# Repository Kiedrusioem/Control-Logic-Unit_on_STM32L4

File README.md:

# Control Logic Unit 

## Project Description
This project focuses on the design and development of a modular Control Logic Unit for a smart buildings system.

The project consists of the three modules:
- **Firware**
- **Extension Board**
- **Software**

## Features
###

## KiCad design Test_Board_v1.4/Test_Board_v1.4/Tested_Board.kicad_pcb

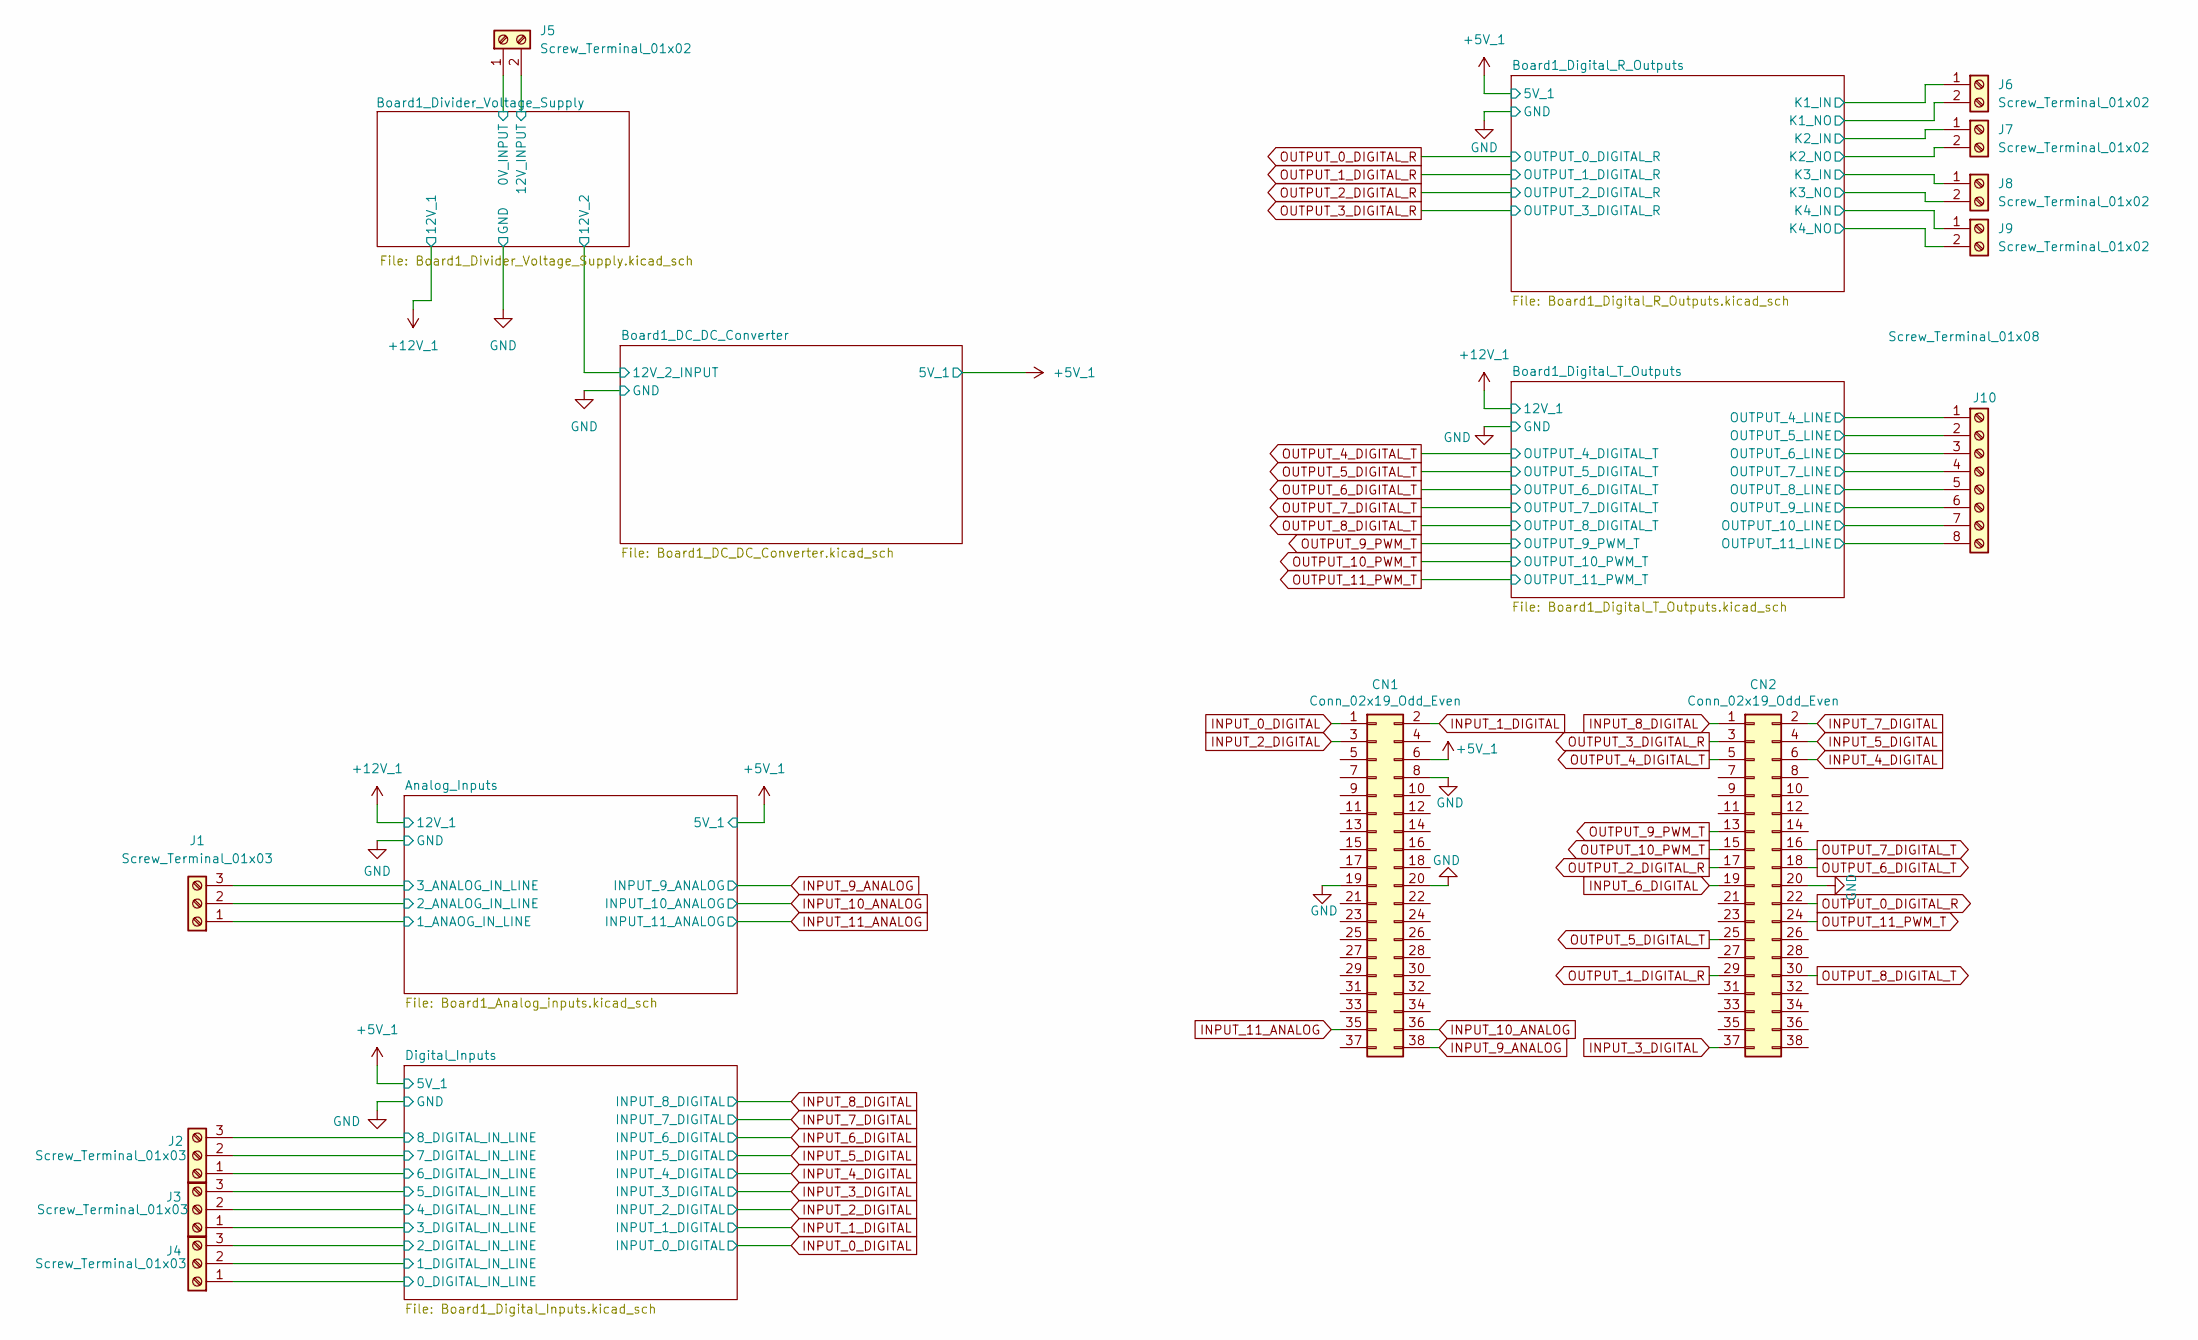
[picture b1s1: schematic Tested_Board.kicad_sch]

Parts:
CN1, CN2: Conn_02x19_Odd_Even; PinSocket_2x19_P2.54mm_Vertical
J1, J2, J3, J4: Screw_Terminal_01x03; TE_282837-3
J5, J6, J7, J8, J9: Screw_Terminal_01x02; TE_282836-2
J10: Screw_Terminal_01x08; TE_282834-8

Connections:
+5V_1: CN1.6; also elsewhere on the board
+12V_1: J5.2; also elsewhere on the board
/Analog_Inputs/1_ANAOG_IN_LINE: J1.1; also elsewhere on the board
/Analog_Inputs/2_ANALOG_IN_LINE: J1.2; also elsewhere on the board
/Analog_Inputs/3_ANALOG_IN_LINE: J1.3; also elsewhere on the board
/Board1_Digital_R_Outputs/K1_IN: J6.1; also elsewhere on the board
/Board1_Digital_R_Outputs/K1_NO: J6.2; also elsewhere on the board
/Board1_Digital_R_Outputs/K2_IN: J7.1; also elsewhere on the board
/Board1_Digital_R_Outputs/K2_NO: J7.2; also elsewhere on the board
/Board1_Digital_R_Outputs/K3_IN: J8.1; also elsewhere on the board
/Board1_Digital_R_Outputs/K3_NO: J8.2; also elsewhere on the board
/Board1_Digital_R_Outputs/K4_IN: J9.1; also elsewhere on the board
/Board1_Digital_R_Outputs/K4_NO: J9.2; also elsewhere on the board
/Board1_Digital_T_Outputs/OUTPUT_4_LINE: J10.1; also elsewhere on the board
/Board1_Digital_T_Outputs/OUTPUT_5_LINE: J10.2; also elsewhere on the board
/Board1_Digital_T_Outputs/OUTPUT_6_LINE: J10.3; also elsewhere on the board
/Board1_Digital_T_Outputs/OUTPUT_7_LINE: J10.4; also elsewhere on the board
/Board1_Digital_T_Outputs/OUTPUT_8_LINE: J10.5; also elsewhere on the board
/Board1_Digital_T_Outputs/OUTPUT_9_LINE: J10.6; also elsewhere on the board
/Board1_Digital_T_Outputs/OUTPUT_10_LINE: J10.7; also elsewhere on the board
/Board1_Digital_T_Outputs/OUTPUT_11_LINE: J10.8; also elsewhere on the board
/Digital_Inputs/MC33204_4_OPAMP_2_P_IN: J4.1; also elsewhere on the board
/Digital_Inputs/MC33204_4_OPAMP_3_P_IN: J4.2; also elsewhere on the board
/Digital_Inputs/MC33204_4_OPAMP_4_P_IN: J4.3; also elsewhere on the board
/Digital_Inputs/MC33204_5_OPAMP_2_P_IN: J3.1; also elsewhere on the board
/Digital_Inputs/MC33204_5_OPAMP_3_P_IN: J3.2; also elsewhere on the board
/Digital_Inputs/MC33204_5_OPAMP_4_P_IN: J3.3; also elsewhere on the board
/Digital_Inputs/MC33204_6_OPAMP_2_P_IN: J2.1; also elsewhere on the board
/Digital_Inputs/MC33204_6_OPAMP_3_P_IN: J2.2; also elsewhere on the board
/Digital_Inputs/MC33204_6_OPAMP_4_P_IN: J2.3; also elsewhere on the board
GND: CN1.8, CN1.19, CN1.20, CN2.20, J5.1; also elsewhere on the board
INPUT_0_DIGITAL: CN1.1; also elsewhere on the board
INPUT_1_DIGITAL: CN1.2; also elsewhere on the board
INPUT_2_DIGITAL: CN1.3; also elsewhere on the board
INPUT_3_DIGITAL: CN2.37; also elsewhere on the board
INPUT_4_DIGITAL: CN2.6; also elsewhere on the board
INPUT_5_DIGITAL: CN2.4; also elsewhere on the board
INPUT_6_DIGITAL: CN2.19; also elsewhere on the board
INPUT_7_DIGITAL: CN2.2; also elsewhere on the board
INPUT_8_DIGITAL: CN2.1; also elsewhere on the board
INPUT_9_ANALOG: CN1.38; also elsewhere on the board
INPUT_10_ANALOG: CN1.36; also elsewhere on the board
INPUT_11_ANALOG: CN1.35; also elsewhere on the board
OUTPUT_0_DIGITAL_R: CN2.22; also elsewhere on the board
OUTPUT_1_DIGITAL_R: CN2.29; also elsewhere on the board
OUTPUT_2_DIGITAL_R: CN2.17; also elsewhere on the board
OUTPUT_3_DIGITAL_R: CN2.3; also elsewhere on the board
OUTPUT_4_DIGITAL_T: CN2.5; also elsewhere on the board
OUTPUT_5_DIGITAL_T: CN2.25; also elsewhere on the board
OUTPUT_6_DIGITAL_T: CN2.18; also elsewhere on the board
OUTPUT_7_DIGITAL_T: CN2.16; also elsewhere on the board
OUTPUT_8_DIGITAL_T: CN2.30; also elsewhere on the board
OUTPUT_9_PWM_T: CN2.13; also elsewhere on the board
OUTPUT_10_PWM_T: CN2.15; also elsewhere on the board
OUTPUT_11_PWM_T: CN2.24; also elsewhere on the board

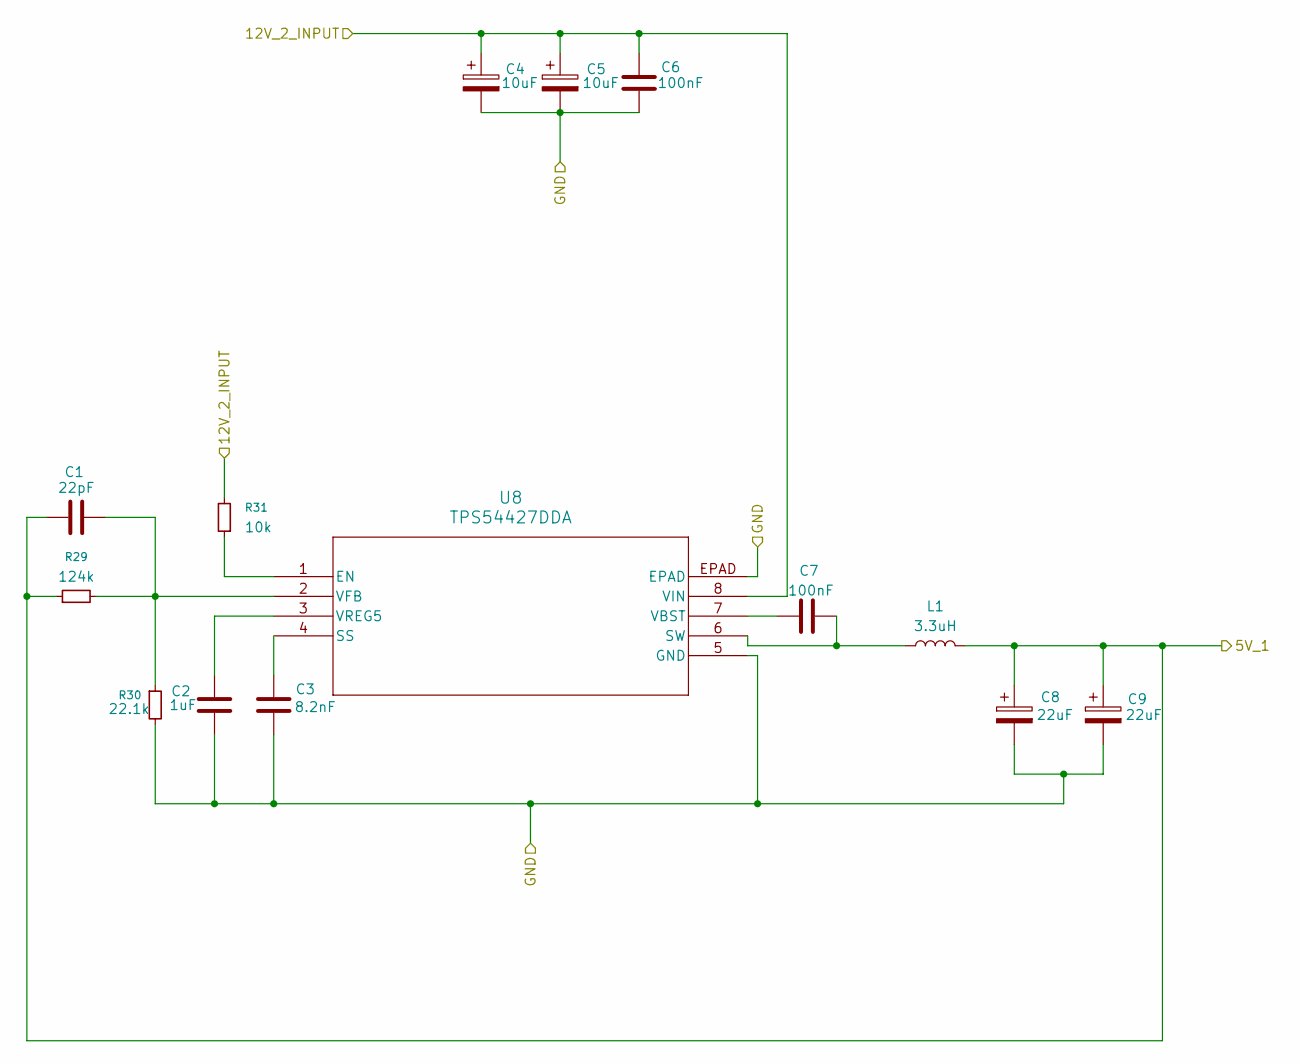
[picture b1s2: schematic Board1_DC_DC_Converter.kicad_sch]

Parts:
C1: 22pF; C_0805_2012Metric_Pad1.18x1.45mm_HandSolder
C2: 1uF; C_1206_3216Metric_Pad1.33x1.80mm_HandSolder
C3: 8.2nF; C_0805_2012Metric_Pad1.18x1.45mm_HandSolder
C4, C5: 10uF; CAP_EEEFK1H100UR
C6, C7: 100nF; C_1206_3216Metric_Pad1.33x1.80mm_HandSolder
C8, C9: 22uF; CAP_EEEFK1H220P
L1: 3.3uH; IND_ETQP4M3R3KFN
R29: 124k; R_0805_2012Metric_Pad1.20x1.40mm_HandSolder
R30: 22.1k; R_0805_2012Metric_Pad1.20x1.40mm_HandSolder
R31: 10k; R_1206_3216Metric_Pad1.30x1.75mm_HandSolder
U8: TPS54427DDA; DDA8_3P1X2P4

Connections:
+5V_1: C1.1, C8.1, C9.1, L1.2, R29.1; also elsewhere on the board
+12V_1: C4.1, C5.1, C6.1, R31.2, U8.8 (VIN); also elsewhere on the board
GND: C2.2, C3.2, C4.2, C5.2, C6.2, C8.2, C9.2, R30.2, U8.5 (GND), U8.EPAD; also elsewhere on the board
unnamed: R31.1, U8.1 (EN)
unnamed: C3.1, U8.4 (SS)
unnamed: C7.2, L1.1, U8.6 (SW)
unnamed: C7.1, U8.7 (VBST)
unnamed: C1.2, R29.2, R30.1, U8.2 (VFB)
unnamed: C2.1, U8.3 (VREG5)

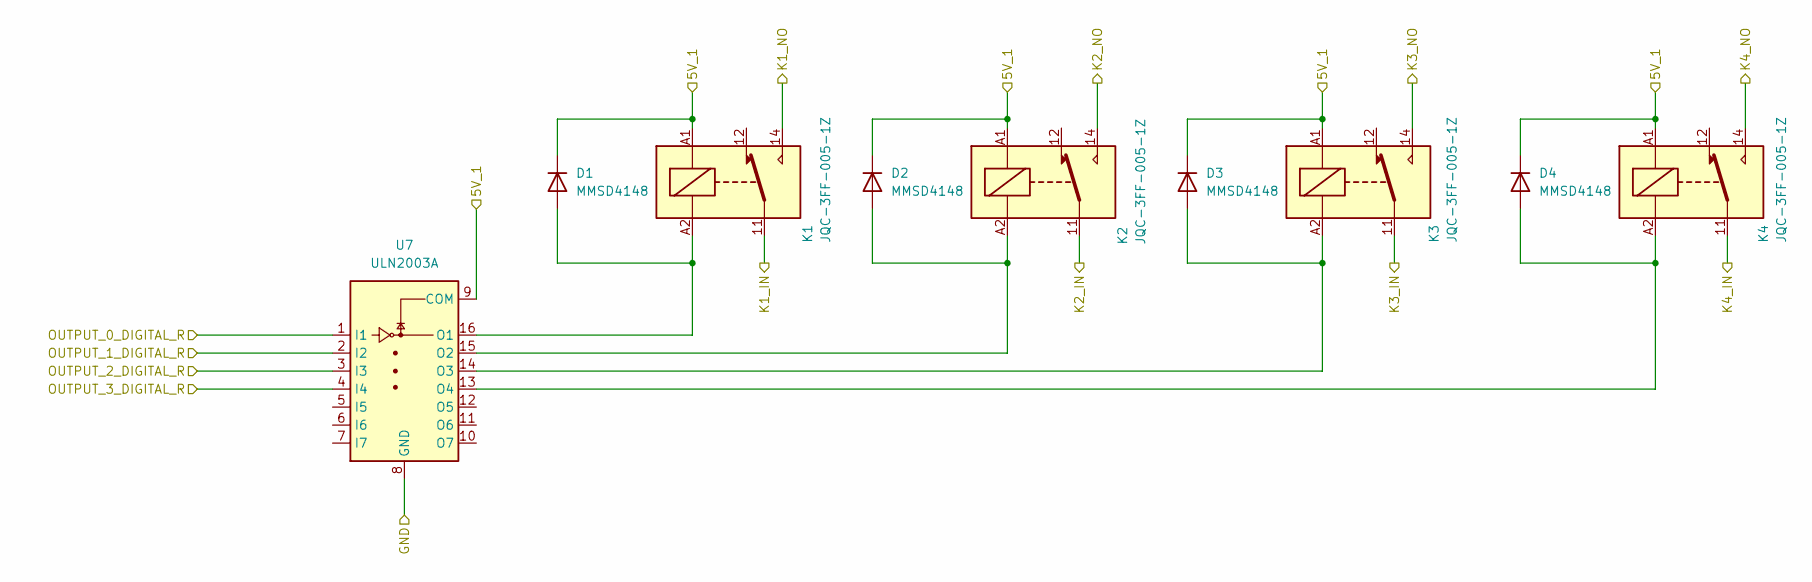
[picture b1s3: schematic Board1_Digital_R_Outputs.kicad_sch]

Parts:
D1, D2, D3, D4: MMSD4148; D_SOD-123
K1, K2, K3, K4: JQC-3FF-005-1Z; Relay_SPDT_Hongfa_JQC-3FF_0XX-1Z
U7: ULN2003A; D0016A_M

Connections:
+5V_1: D1.1 (K), D2.1 (K), D3.1 (K), D4.1 (K), K1.A1, K2.A1, K3.A1, K4.A1, U7.9 (COM); also elsewhere on the board
/Board1_Digital_R_Outputs/K1_IN: K1.11; also elsewhere on the board
/Board1_Digital_R_Outputs/K1_NO: K1.14; also elsewhere on the board
/Board1_Digital_R_Outputs/K2_IN: K2.11; also elsewhere on the board
/Board1_Digital_R_Outputs/K2_NO: K2.14; also elsewhere on the board
/Board1_Digital_R_Outputs/K3_IN: K3.11; also elsewhere on the board
/Board1_Digital_R_Outputs/K3_NO: K3.14; also elsewhere on the board
/Board1_Digital_R_Outputs/K4_IN: K4.11; also elsewhere on the board
/Board1_Digital_R_Outputs/K4_NO: K4.14; also elsewhere on the board
GND: U7.8 (GND); also elsewhere on the board
unnamed: D1.2 (A), K1.A2, U7.16 (O1)
unnamed: D2.2 (A), K2.A2, U7.15 (O2)
unnamed: D3.2 (A), K3.A2, U7.14 (O3)
unnamed: D4.2 (A), K4.A2, U7.13 (O4)
OUTPUT_0_DIGITAL_R: U7.1 (I1); also elsewhere on the board
OUTPUT_1_DIGITAL_R: U7.2 (I2); also elsewhere on the board
OUTPUT_2_DIGITAL_R: U7.3 (I3); also elsewhere on the board
OUTPUT_3_DIGITAL_R: U7.4 (I4); also elsewhere on the board

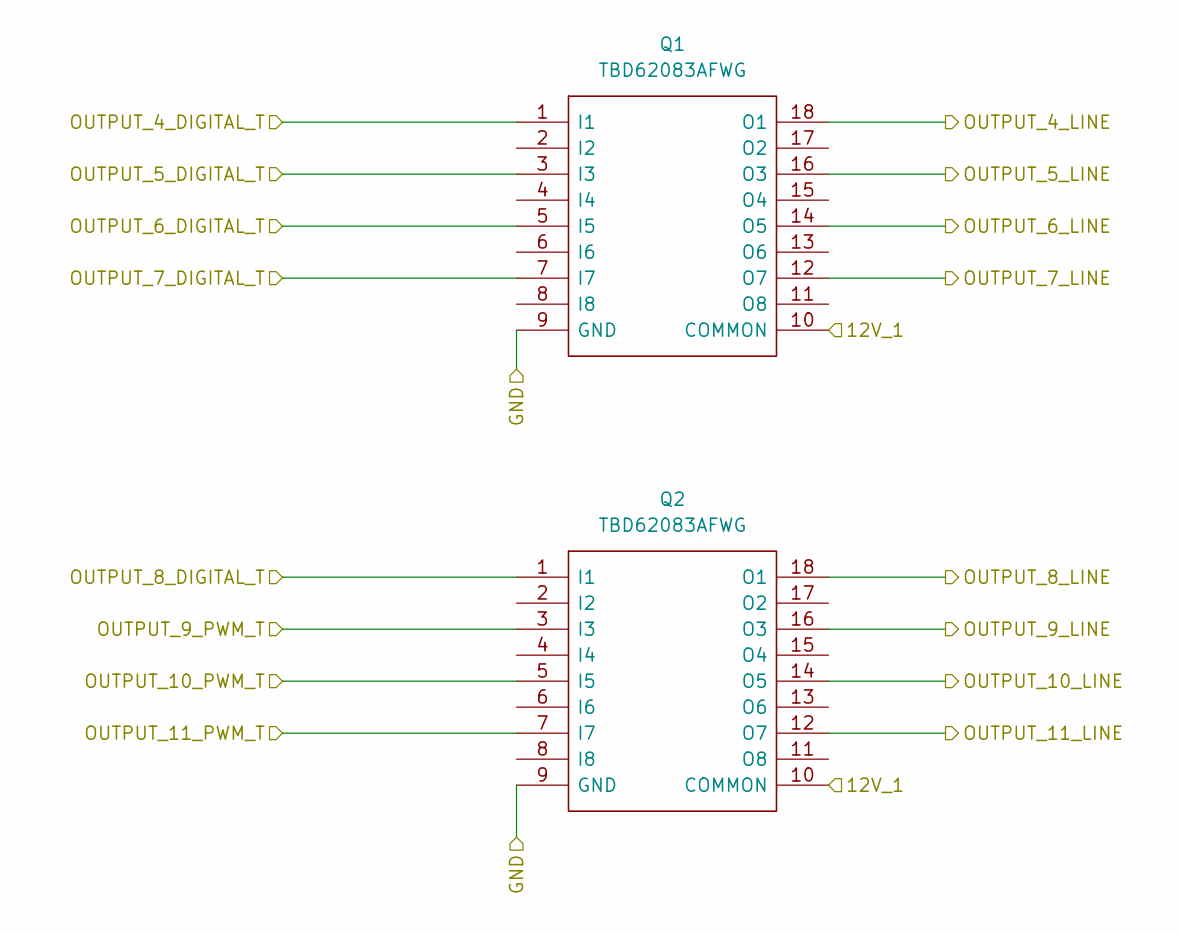
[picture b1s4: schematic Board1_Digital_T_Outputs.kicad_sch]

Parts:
Q1, Q2: TBD62083AFWG; SOIC127P1032X285-18N; Manufacturer_Part_Number TBD62083AFWG; Mouser Part Number 757-TBD62083AFWG

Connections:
+12V_1: Q1.10 (COMMON), Q2.10 (COMMON); also elsewhere on the board
/Board1_Digital_T_Outputs/OUTPUT_4_LINE: Q1.18 (O1); also elsewhere on the board
/Board1_Digital_T_Outputs/OUTPUT_5_LINE: Q1.16 (O3); also elsewhere on the board
/Board1_Digital_T_Outputs/OUTPUT_6_LINE: Q1.14 (O5); also elsewhere on the board
/Board1_Digital_T_Outputs/OUTPUT_7_LINE: Q1.12 (O7); also elsewhere on the board
/Board1_Digital_T_Outputs/OUTPUT_8_LINE: Q2.18 (O1); also elsewhere on the board
/Board1_Digital_T_Outputs/OUTPUT_9_LINE: Q2.16 (O3); also elsewhere on the board
/Board1_Digital_T_Outputs/OUTPUT_10_LINE: Q2.14 (O5); also elsewhere on the board
/Board1_Digital_T_Outputs/OUTPUT_11_LINE: Q2.12 (O7); also elsewhere on the board
GND: Q1.9 (GND), Q2.9 (GND); also elsewhere on the board
OUTPUT_4_DIGITAL_T: Q1.1 (I1); also elsewhere on the board
OUTPUT_5_DIGITAL_T: Q1.3 (I3); also elsewhere on the board
OUTPUT_6_DIGITAL_T: Q1.5 (I5); also elsewhere on the board
OUTPUT_7_DIGITAL_T: Q1.7 (I7); also elsewhere on the board
OUTPUT_8_DIGITAL_T: Q2.1 (I1); also elsewhere on the board
OUTPUT_9_PWM_T: Q2.3 (I3); also elsewhere on the board
OUTPUT_10_PWM_T: Q2.5 (I5); also elsewhere on the board
OUTPUT_11_PWM_T: Q2.7 (I7); also elsewhere on the board

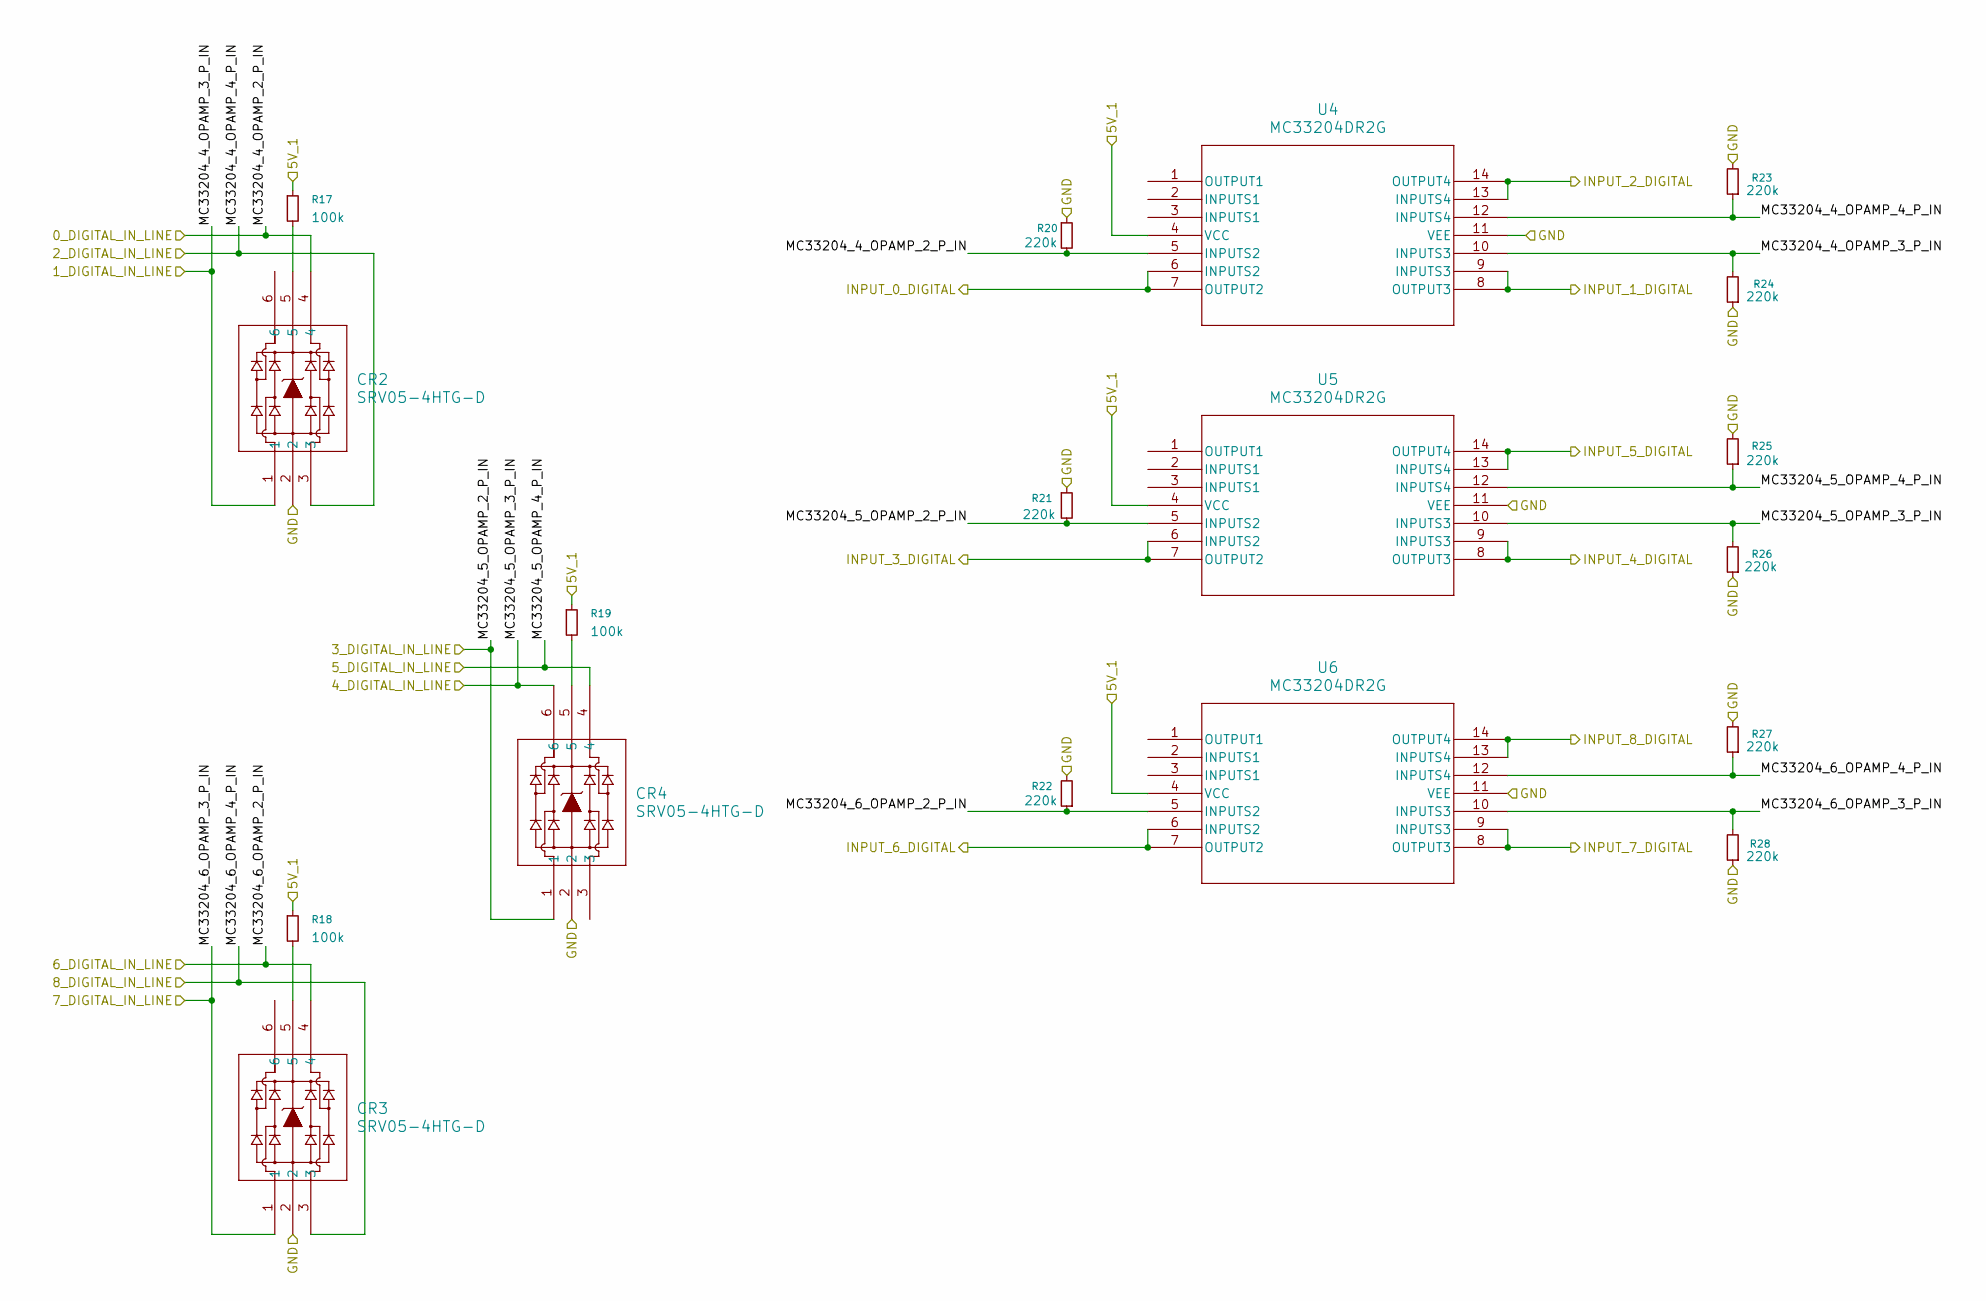
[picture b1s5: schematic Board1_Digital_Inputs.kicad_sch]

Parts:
CR2, CR3, CR4: SRV05-4HTG-D; SOIC6_SOT23-6_CRA_LTF
R17, R18, R19: 100k; R_1206_3216Metric_Pad1.30x1.75mm_HandSolder
R20, R21, R22, R23, R24, R25, R26, R27, R28: 220k; R_1206_3216Metric_Pad1.30x1.75mm_HandSolder
U4, U5, U6: MC33204DR2G; SOIC-14_NB_ONS

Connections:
+5V_1: R17.1, R18.1, R19.1, U4.4 (VCC), U5.4 (VCC), U6.4 (VCC); also elsewhere on the board
/Digital_Inputs/MC33204_4_OPAMP_2_P_IN: CR2.4, R20.2, U4.5 (INPUTS2); also elsewhere on the board
/Digital_Inputs/MC33204_4_OPAMP_3_P_IN: CR2.1, R24.2, U4.10 (INPUTS3); also elsewhere on the board
/Digital_Inputs/MC33204_4_OPAMP_4_P_IN: CR2.3, R23.1, U4.12 (INPUTS4); also elsewhere on the board
/Digital_Inputs/MC33204_5_OPAMP_2_P_IN: CR4.1, R21.2, U5.5 (INPUTS2); also elsewhere on the board
/Digital_Inputs/MC33204_5_OPAMP_3_P_IN: CR4.6, R26.2, U5.10 (INPUTS3); also elsewhere on the board
/Digital_Inputs/MC33204_5_OPAMP_4_P_IN: CR4.4, R25.1, U5.12 (INPUTS4); also elsewhere on the board
/Digital_Inputs/MC33204_6_OPAMP_2_P_IN: CR3.4, R22.1, U6.5 (INPUTS2); also elsewhere on the board
/Digital_Inputs/MC33204_6_OPAMP_3_P_IN: CR3.1, R28.2, U6.10 (INPUTS3); also elsewhere on the board
/Digital_Inputs/MC33204_6_OPAMP_4_P_IN: CR3.3, R27.1, U6.12 (INPUTS4); also elsewhere on the board
GND: CR2.2, CR3.2, CR4.2, R20.1, R21.1, R22.2, R23.2, R24.1, R25.2, R26.1, R27.2, R28.1, U4.11 (VEE), U5.11 (VEE), U6.11 (VEE); also elsewhere on the board
INPUT_0_DIGITAL: U4.6 (INPUTS2), U4.7 (OUTPUT2); also elsewhere on the board
INPUT_1_DIGITAL: U4.8 (OUTPUT3), U4.9 (INPUTS3); also elsewhere on the board
INPUT_2_DIGITAL: U4.13 (INPUTS4), U4.14 (OUTPUT4); also elsewhere on the board
INPUT_3_DIGITAL: U5.6 (INPUTS2), U5.7 (OUTPUT2); also elsewhere on the board
INPUT_4_DIGITAL: U5.8 (OUTPUT3), U5.9 (INPUTS3); also elsewhere on the board
INPUT_5_DIGITAL: U5.13 (INPUTS4), U5.14 (OUTPUT4); also elsewhere on the board
INPUT_6_DIGITAL: U6.6 (INPUTS2), U6.7 (OUTPUT2); also elsewhere on the board
INPUT_7_DIGITAL: U6.8 (OUTPUT3), U6.9 (INPUTS3); also elsewhere on the board
INPUT_8_DIGITAL: U6.13 (INPUTS4), U6.14 (OUTPUT4); also elsewhere on the board
unnamed: CR2.5, R17.2
unnamed: CR3.5, R18.2
unnamed: CR4.5, R19.2

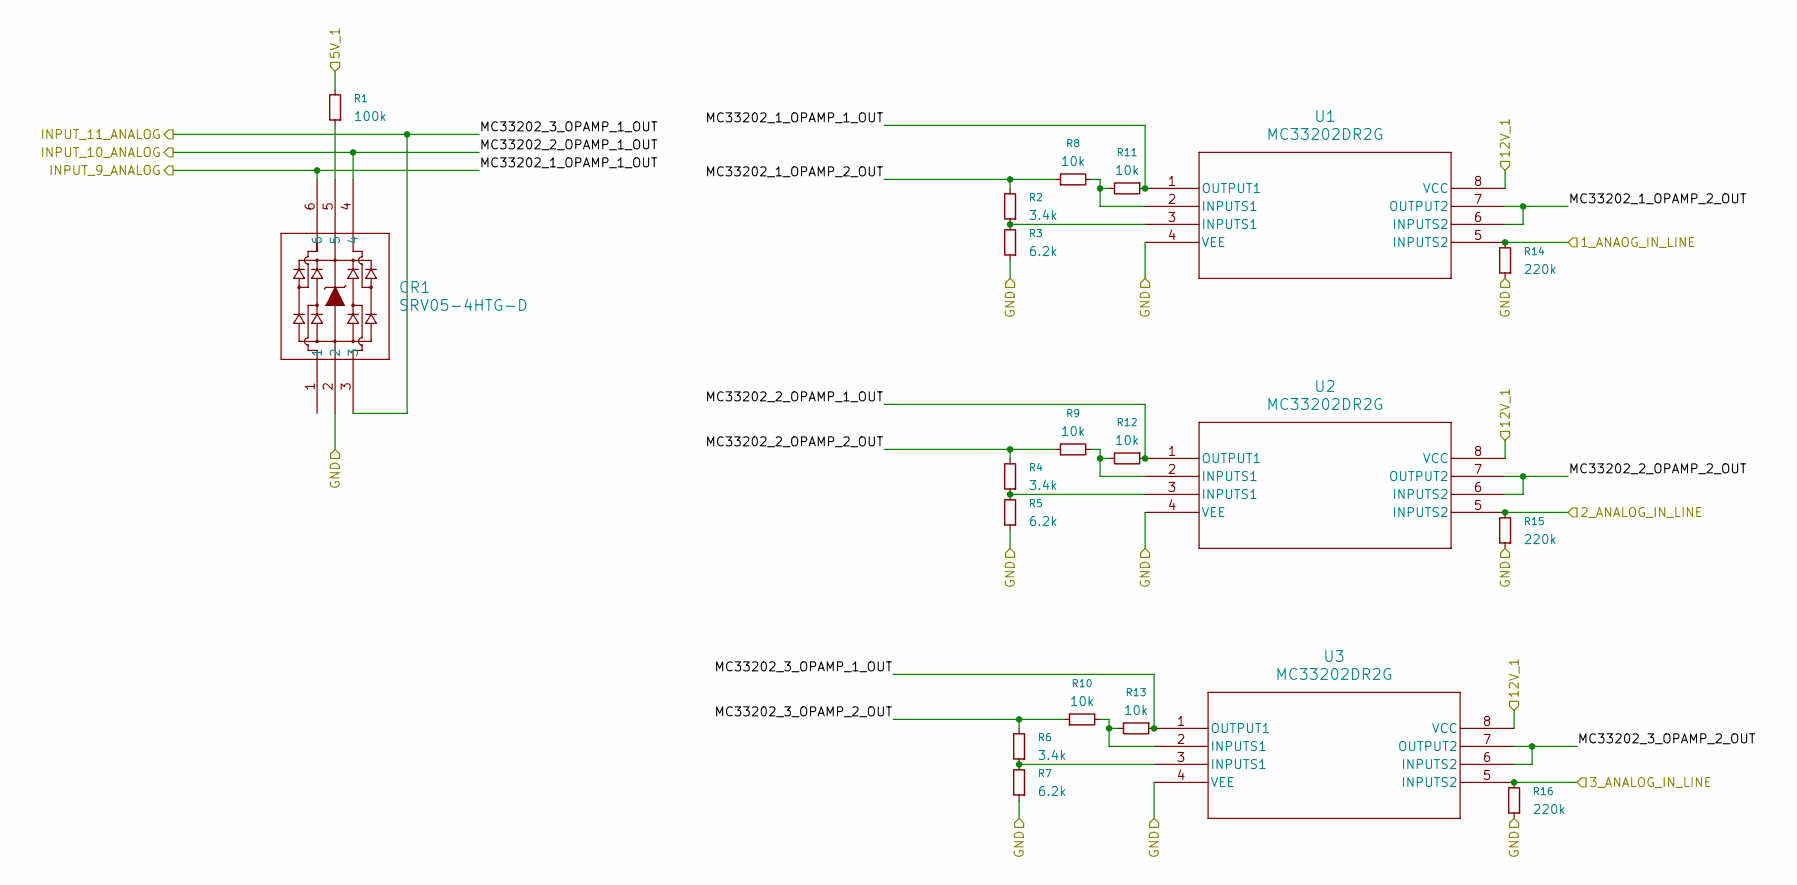
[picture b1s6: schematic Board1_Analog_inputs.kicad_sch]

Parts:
CR1: SRV05-4HTG-D; SOIC6_SOT23-6_CRA_LTF
R1: 100k; R_1206_3216Metric_Pad1.30x1.75mm_HandSolder
R2, R4, R6: 3.4k; R_1206_3216Metric_Pad1.30x1.75mm_HandSolder
R3, R5, R7: 6.2k; R_0805_2012Metric_Pad1.20x1.40mm_HandSolder
R8, R9, R10, R11, R12, R13: 10k; R_1206_3216Metric_Pad1.30x1.75mm_HandSolder
R14, R15, R16: 220k; R_1206_3216Metric_Pad1.30x1.75mm_HandSolder
U1, U2, U3: MC33202DR2G; SOIC8_ONS

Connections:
+5V_1: R1.2; also elsewhere on the board
+12V_1: U1.8 (VCC), U2.8 (VCC), U3.8 (VCC); also elsewhere on the board
/Analog_Inputs/1_ANAOG_IN_LINE: R14.2, U1.5 (INPUTS2); also elsewhere on the board
/Analog_Inputs/2_ANALOG_IN_LINE: R15.2, U2.5 (INPUTS2); also elsewhere on the board
/Analog_Inputs/3_ANALOG_IN_LINE: R16.2, U3.5 (INPUTS2); also elsewhere on the board
/Analog_Inputs/MC33202_1_OPAMP_2_OUT: R2.2, R8.1, U1.6 (INPUTS2), U1.7 (OUTPUT2)
/Analog_Inputs/MC33202_2_OPAMP_2_OUT: R4.2, R9.1, U2.6 (INPUTS2), U2.7 (OUTPUT2)
/Analog_Inputs/MC33202_3_OPAMP_2_OUT: R6.2, R10.1, U3.6 (INPUTS2), U3.7 (OUTPUT2)
GND: CR1.2, R3.1, R5.1, R7.1, R14.1, R15.1, R16.1, U1.4 (VEE), U2.4 (VEE), U3.4 (VEE); also elsewhere on the board
INPUT_9_ANALOG: CR1.6, R11.1, U1.1 (OUTPUT1); also elsewhere on the board
INPUT_10_ANALOG: CR1.4, R12.1, U2.1 (OUTPUT1); also elsewhere on the board
INPUT_11_ANALOG: CR1.3, R13.1, U3.1 (OUTPUT1); also elsewhere on the board
unnamed: CR1.5, R1.1
unnamed: R2.1, R3.2, U1.3 (INPUTS1)
unnamed: R4.1, R5.2, U2.3 (INPUTS1)
unnamed: R6.1, R7.2, U3.3 (INPUTS1)
unnamed: R10.2, R13.2, U3.2 (INPUTS1)
unnamed: R8.2, R11.2, U1.2 (INPUTS1)
unnamed: R9.2, R12.2, U2.2 (INPUTS1)

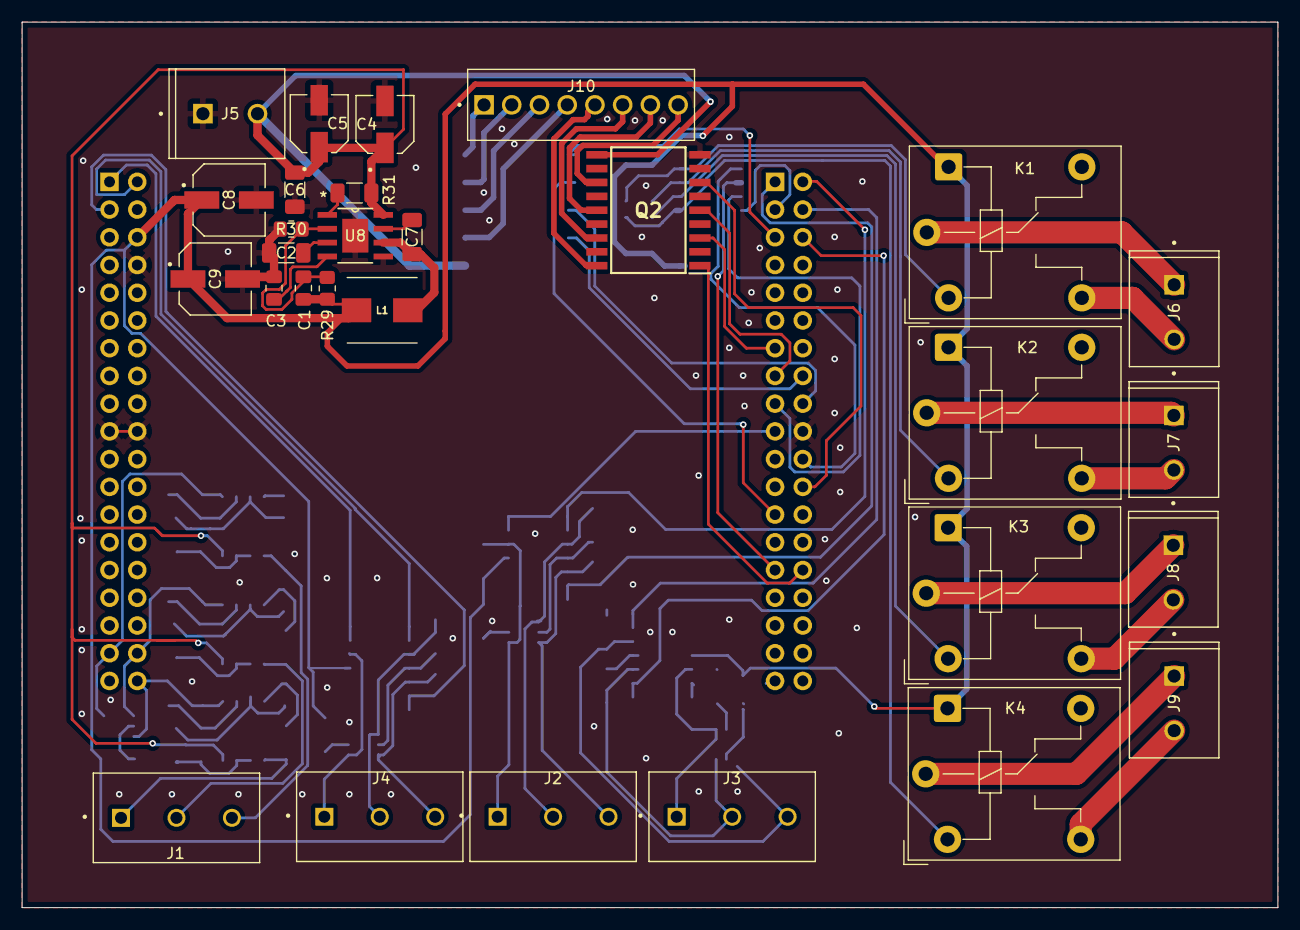
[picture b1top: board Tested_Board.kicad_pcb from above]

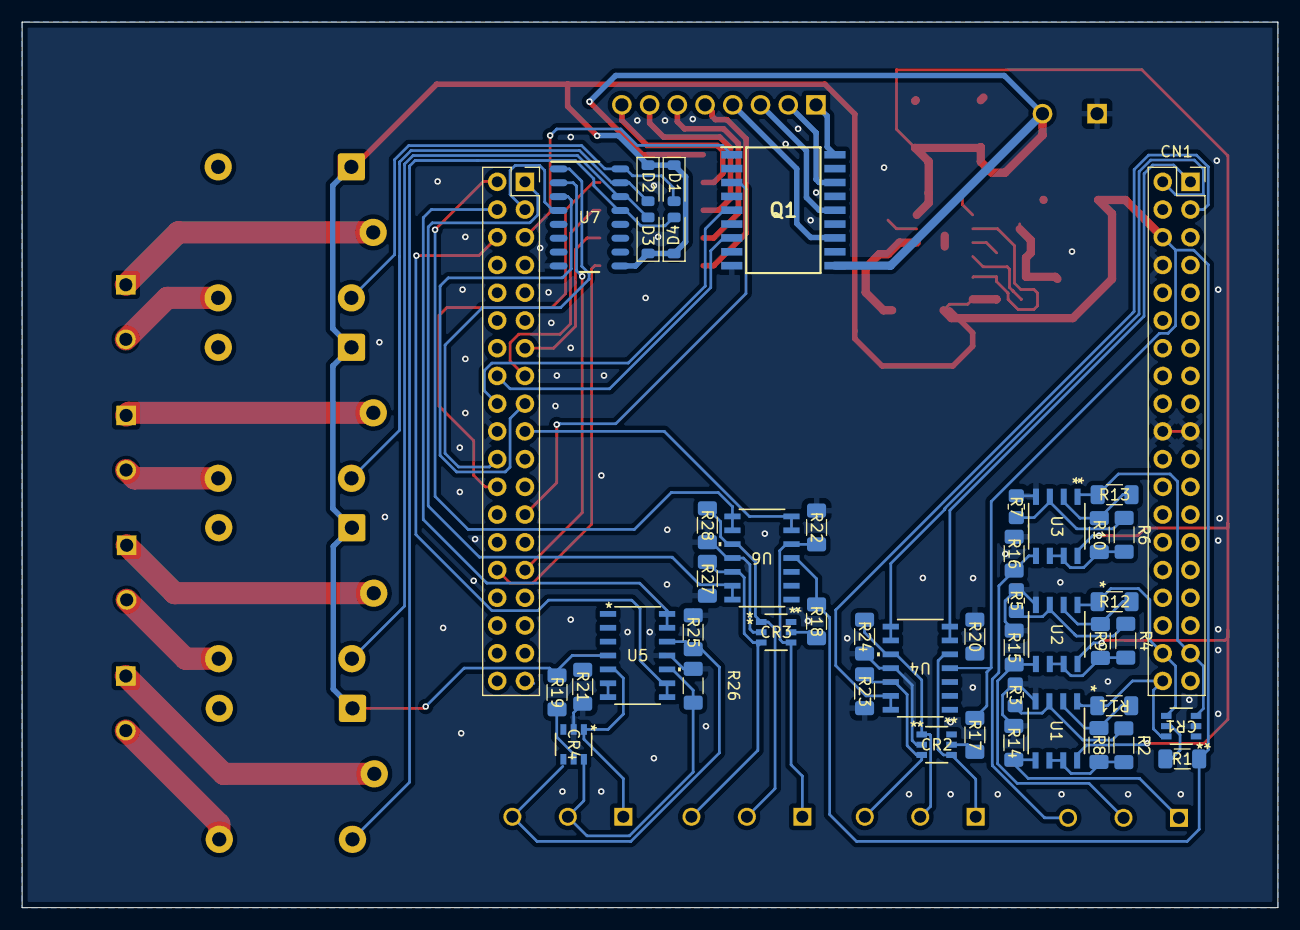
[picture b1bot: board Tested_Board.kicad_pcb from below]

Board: 2 copper layers, 115.0 x 81.1 mm, 75 parts (46 on the bottom side), 78 nets.

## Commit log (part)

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2026-02-22 Newer Commit
